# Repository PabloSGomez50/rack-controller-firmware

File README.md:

# Sistema de Monitoreo y Control IoT para Rack de Telecomunicaciones

Este repositorio contiene el código fuente y la documentación para un dispositivo de monitoreo y control desarrollado para un proveedor de internet. El dispositivo se diseñó para ser instalado en un rack de telecomunicaciones Huawei y se comunica a través de Ethernet para monitorear condiciones ambientales y controlar componentes del rack.

https://github.com/nicolasottone/rack-controller-firmware/assets/64184394/97a96b82-3d05-4193-a270-a76540e8a40f

## Resumen

Se consume la API REST de Google Firebase desde el microcontrolador ESP32 para enviar y recibir datos mediante HTTPS. Desde una aplicación web se accede a los mismos en tiempo real y se controla el dispositivo a distancia. 

**Características:**

* **Monitoreo:**
    * Temperatura ambiental y de contacto.
    * Humedad relativa.
    * Presencia de humo.
    * Estado de la puerta del rack (abierta/cerrada).
* **Control:**
    * 3 ventiladores con control PWM y tacometría.
    * Un relé para control remoto de periféricos.
    * Buzzer para alertas locales.
* **Comunicación:**
    * Conexión Ethernet a través de un módulo ENC28J60.
    * Interfaz web para monitoreo y control remoto.
* **Integración con Firebase:**
    * Envío de datos a la Realtime Database de Firebase.
    * Uso del SDK de Firebase en el lado del cliente para recibir y enviar datos.
    * Conección en tiempo real por Websockets.
    * Autenticación de usuarios con Firebase Auth.
* **Interfaz de Usuario:**
    * Aplicación web con gráficos de datos en tiempo real, KPIs, alertas graficas y panel de configuración.
    * Control remoto de ventiladores, relé y configuración del dispositivo.
* **Hardware:**
    * Microcontrolador ESP32 con RTOS.
    * Modulo Ethernet ENC28J60.
    * Sensores de temperatura, humedad, humo y switch magnético.
    * * Sensor NTC 10K de alta precisión.
    * * Termohigrómetro WS302A1T4
    * * Sensor de Humo JTY-GD-S839
    * Protección contra polaridad inversa.
    * Etapas de acondicionamiento de señales (etapa de potencias, opto-acopladores, etc).
    * Pantalla LCD de 2x16 caracteres.
    * Fuente Step-Up de 48V, fuente Step-Down 12V y reguladores lineales 5V.
    * Conectores HOWSING.

**Arquitectura:**

* **Hardware:**
    * El hardware se basa en el ESP32, un microcontrolador de doble núcleo y ADC incorporados.
    * El módulo ENC28J60 proporciona la conectividad Ethernet.
    * Los sensores, actuadores y periféricos se conectan al ESP32 a través de interfaces GPIO.
* **Software:**
    * El software se divide en dos tareas principales, una para cada núcleo del ESP32:
        * **Núcleo 0:** Lee datos de los sensores, controla los actuadores y maneja los estados del dispositivo.
        * **Núcleo 1:** Envía y recibe datos al servidor a través de una conexión HTTPS.
    * La comunicación con el servidor se realiza mediante peticiones POST y GET a la API REST de Firebase.
    * La aplicación web utiliza WebSockets para recibir actualizaciones de datos en tiempo real.
    * La interfaz de usuario se desarrolló con HTML, CSS, JavaScript y jQuery.

**Calibración:**

* Los ADC fueron calibrados digitalmente usando un multímetro como referencia.
* El termistor NTC se calibró usando el método Steinhart-Hart.
* Se realizaron pruebas de funcionamiento de los ventiladores y se ajustó el control PWM para un óptimo desempeño.

**Niveles de Tensión:**

* El dispositivo opera internamente a 4 niveles de tensión: 48V, 12V, 5V y 3,3V.
* Se puede alimentar con un rango de tensión de 12V a 30V.

**Case:**

* Se diseño un case que consta de dos partes unidas por tornillos para proteger el dispotivo.
* Se utilizo SolidWorks y se diseño para ser impreso en 3D. 

**Documentación:**

* Este README.md proporciona una descripción general del proyecto.
* Los archivos de código fuente contienen comentarios detallados en español.
* La documentación adicional se encuentra en la carpeta `assets`. (Tambien se puede acceder al video con la calidad original).

## Assets:
### Esquema del circuito:
* 

### Imagenes del case:
* 
* 
* 

### Board:
* 
*

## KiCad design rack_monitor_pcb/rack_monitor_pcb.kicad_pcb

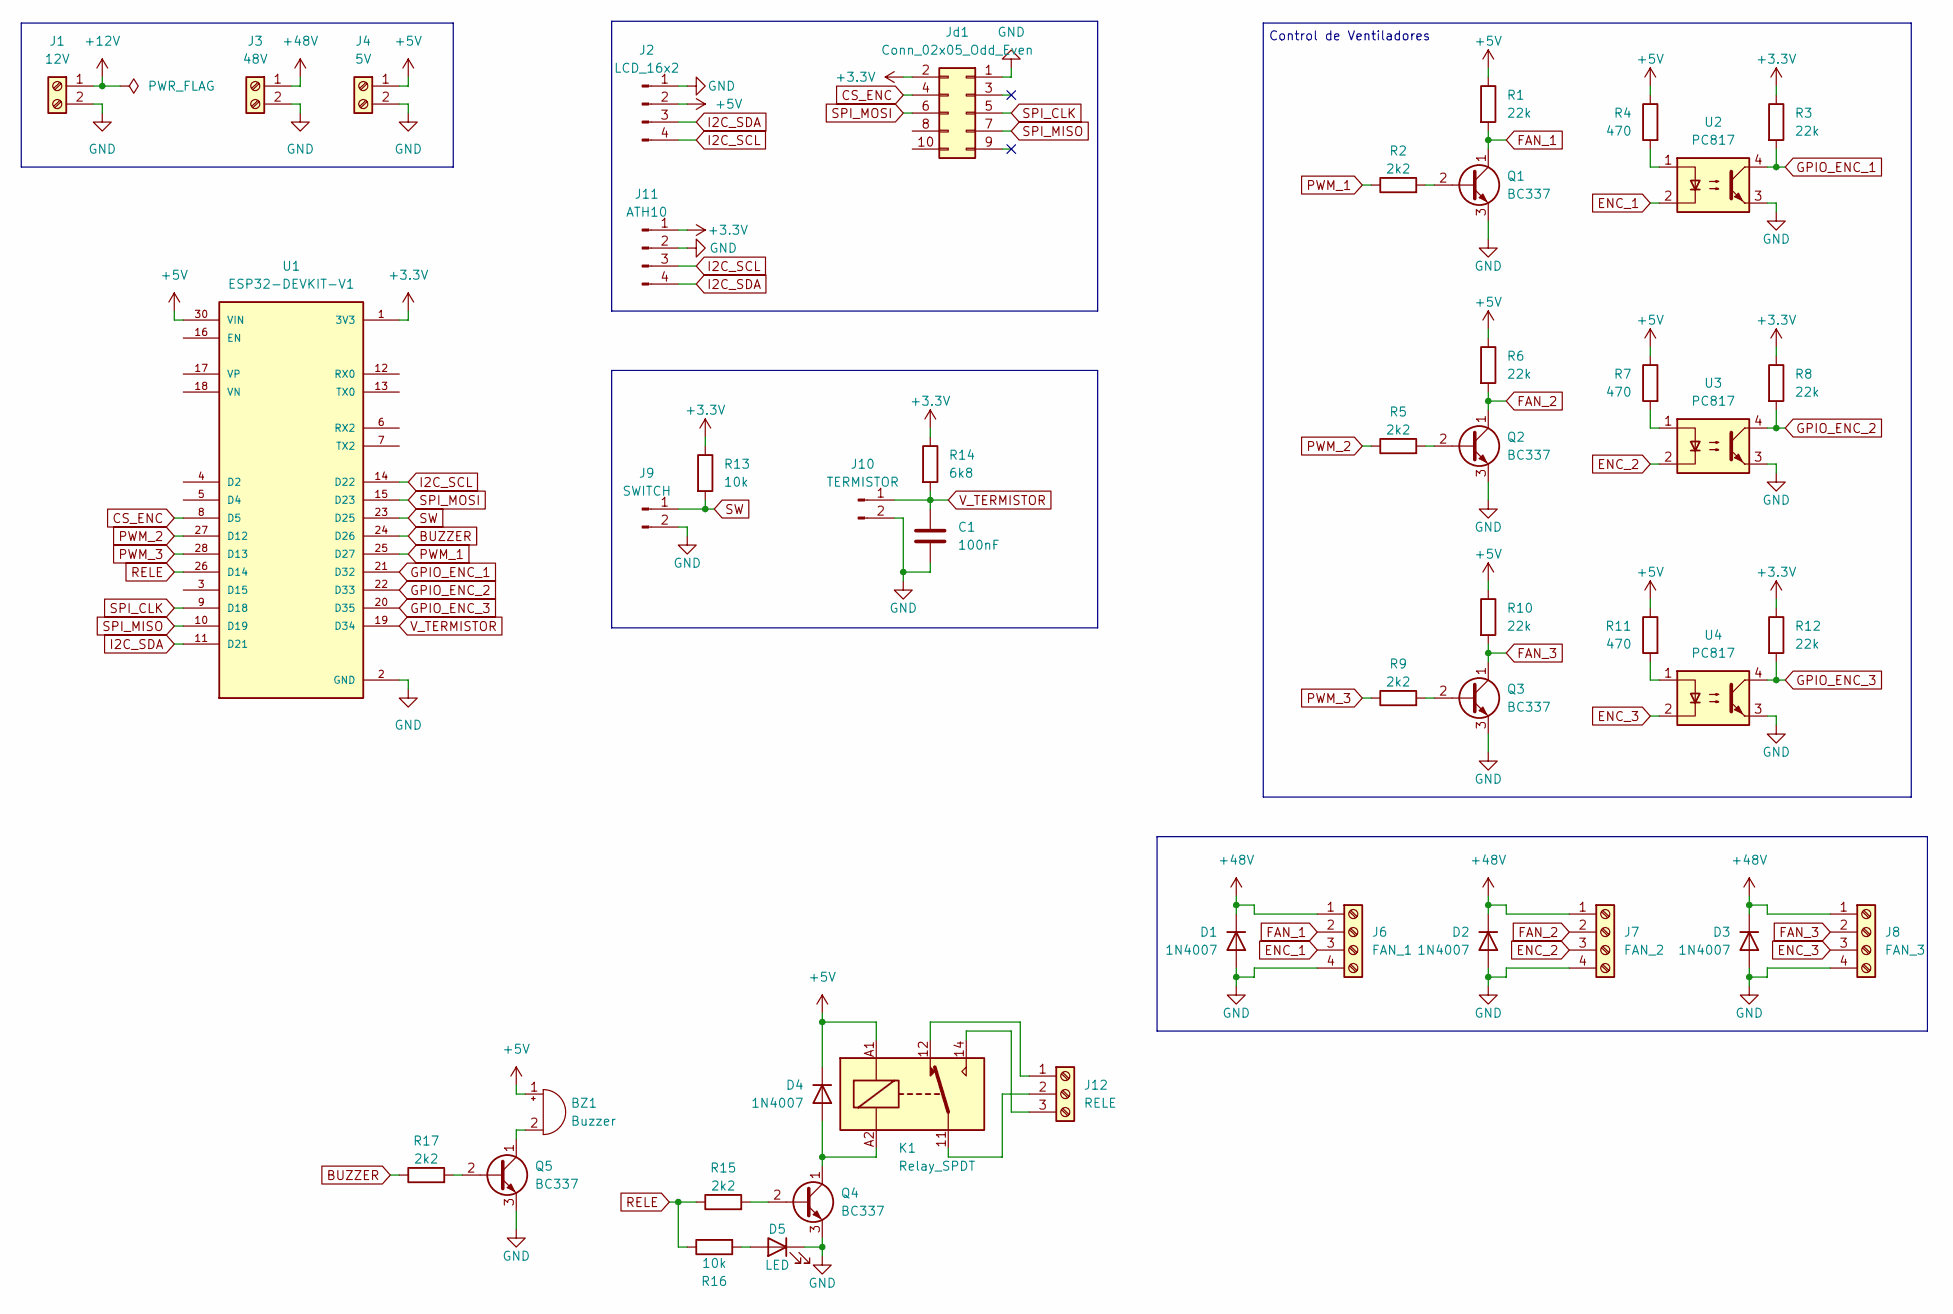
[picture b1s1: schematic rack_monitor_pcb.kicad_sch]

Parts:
BZ1: Buzzer; Buzzer_12x9.5RM7.6
C1: 100nF; C_Disc_D3.4mm_W2.1mm_P2.50mm
D1, D2, D3, D4: 1N4007; D_DO-41_SOD81_P10.16mm_Horizontal
D5: LED; LED_D3.0mm
J1: 12V; TerminalBlock_Phoenix_MKDS-1,5-2-5.08_1x02_P5.08mm_Horizont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
J2: LCD_16x2; PinHeader_1x04_P2.54mm_Vertical
J3: 48V; TerminalBlock_Phoenix_MKDS-1,5-2-5.08_1x02_P5.08mm_Horizont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
J4: 5V; TerminalBlock_Phoenix_MKDS-1,5-2-5.08_1x02_P5.08mm_Horizont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
J6: FAN_1; Molex_KK-254_AE-6410-04A_1x04_P2.54mm_Vertical
J7: FAN_2; Molex_KK-254_AE-6410-04A_1x04_P2.54mm_Vertical
J8: FAN_3; Molex_KK-254_AE-6410-04A_1x04_P2.54mm_Vertical
J9: SWITCH; Molex_KK-254_AE-6410-02A_1x02_P2.54mm_Vertical
J10: TERMISTOR; Molex_KK-254_AE-6410-02A_1x02_P2.54mm_Vertical
J11: ATH10; PinHeader_1x04_P2.54mm_Vertical
J12: RELE; TerminalBlock_Phoenix_MKDS-1,5-3-5.08_1x03_P5.08mm_Horizont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
Jd1: Conn_02x05_Odd_Even; PinHeader_2x05_P2.54mm_Vertical
K1: Relay_SPDT; Relay_SPDT_Hongfa_HF3F-L-xx-1ZL1T
Q1, Q2, Q3, Q4, Q5: BC337; TO-92_Inline_Wide
R1, R3, R6, R8, R10, R12: 22k; R_Axial_DIN0207_L6.3mm_D2.5mm_P10.16mm_Horizontal
R2, R5, R9, R15, R17: 2k2; R_Axial_DIN0207_L6.3mm_D2.5mm_P10.16mm_Horizontal
R4, R7, R11: 470; R_Axial_DIN0207_L6.3mm_D2.5mm_P10.16mm_Horizontal
R13, R16: 10k; R_Axial_DIN0207_L6.3mm_D2.5mm_P10.16mm_Horizontal
R14: 6k8; R_Axial_DIN0207_L6.3mm_D2.5mm_P10.16mm_Horizontal
U1: ESP32-DEVKIT-V1; MODULE_ESP32_DEVKIT_V1; PARTREV N/A
U2, U3, U4: PC817; DIP-4_W7.62mm

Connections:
+3.3V: J11.1, Jd1.2, R3.1, R8.1, R12.1, R13.1, R14.1, U1.1 (3V3)
+5V: BZ1.1 (+), D4.1 (K), J2.2, J4.1, K1.A1, R1.1, R4.1, R6.1, R7.1, R10.1, R11.1, U1.30 (VIN)
+12V: J1.1
+48V: D1.1 (K), D2.1 (K), D3.1 (K), J3.1, J6.1, J7.1, J8.1
BUZZER: R17.1, U1.24 (D26)
CS_ENC: Jd1.4, U1.8 (D5)
ENC_1: J6.3, U2.2
ENC_2: J7.3, U3.2
ENC_3: J8.3, U4.2
FAN_1: J6.2, Q1.1 (C), R1.2
FAN_2: J7.2, Q2.1 (C), R6.2
FAN_3: J8.2, Q3.1 (C), R10.2
GND: C1.2, D1.2 (A), D2.2 (A), D3.2 (A), D5.1 (K), J1.2, J2.1, J3.2, J4.2, J6.4, J7.4, J8.4, J9.2, J10.2, J11.2, Jd1.1, Q1.3 (E), Q2.3 (E), Q3.3 (E), Q4.3 (E), Q5.3 (E), U1.2 (GND), U1.29 (GND), U2.3, U3.3, U4.3
GPIO_ENC_1: R3.2, U1.21 (D32), U2.4
GPIO_ENC_2: R8.2, U1.22 (D33), U3.4
GPIO_ENC_3: R12.2, U1.20 (D35), U4.4
I2C_SCL: J2.4, J11.3, U1.14 (D22)
I2C_SDA: J2.3, J11.4, U1.11 (D21)
unnamed: BZ1.2 (-), Q5.1 (C)
unnamed: D4.2 (A), K1.A2, Q4.1 (C)
unnamed: D5.2 (A), R16.2
unnamed: J12.1, K1.12
unnamed: J12.2, K1.11
unnamed: J12.3, K1.14
unnamed: Q1.2 (B), R2.2
unnamed: Q2.2 (B), R5.2
unnamed: Q3.2 (B), R9.2
unnamed: Q4.2 (B), R15.2
unnamed: Q5.2 (B), R17.2
unnamed: R4.2, U2.1
unnamed: R7.2, U3.1
unnamed: R11.2, U4.1
PWM_1: R2.1, U1.25 (D27)
PWM_2: R5.1, U1.27 (D12)
PWM_3: R9.1, U1.28 (D13)
RELE: R15.1, R16.1, U1.26 (D14)
SPI_CLK: Jd1.5, U1.9 (D18)
SPI_MISO: Jd1.7, U1.10 (D19)
SPI_MOSI: Jd1.6, U1.15 (D23)
SW: J9.1, R13.2, U1.23 (D25)
V_TERMISTOR: C1.1, J10.1, R14.2, U1.19 (D34)

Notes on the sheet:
Control de Ventiladores

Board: 2 copper layers, 46 parts (0 on the bottom side), 40 nets, no tracks yet.

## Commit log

2024-07-03 assets upload
2024-07-03 Fixed README.md not show images
2026-02-19 chore: compile in new version of esp32 lib
2026-02-27 chore: split in tasks
2026-03-02 fix: test EthernetENC with correct module
2026-03-02 chore: compile version of initial tasks
2026-03-05 chore: add conection over HTTPClient
2026-03-06 chore: remove unused global vars, isolate requests in parser and display writing
2026-03-11 chore: make schematic
2026-03-11 fix: endpoints for EthernetClient
2026-03-31 chore: fix http comunication via WiFi tested
2026-04-24 chore: test disable telegram in ethernet
